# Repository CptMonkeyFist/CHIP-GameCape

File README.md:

# CHIP-GameCape

This is a cape being designed for the CHIP embedded computer. See the LICENSE.txt file for license details.

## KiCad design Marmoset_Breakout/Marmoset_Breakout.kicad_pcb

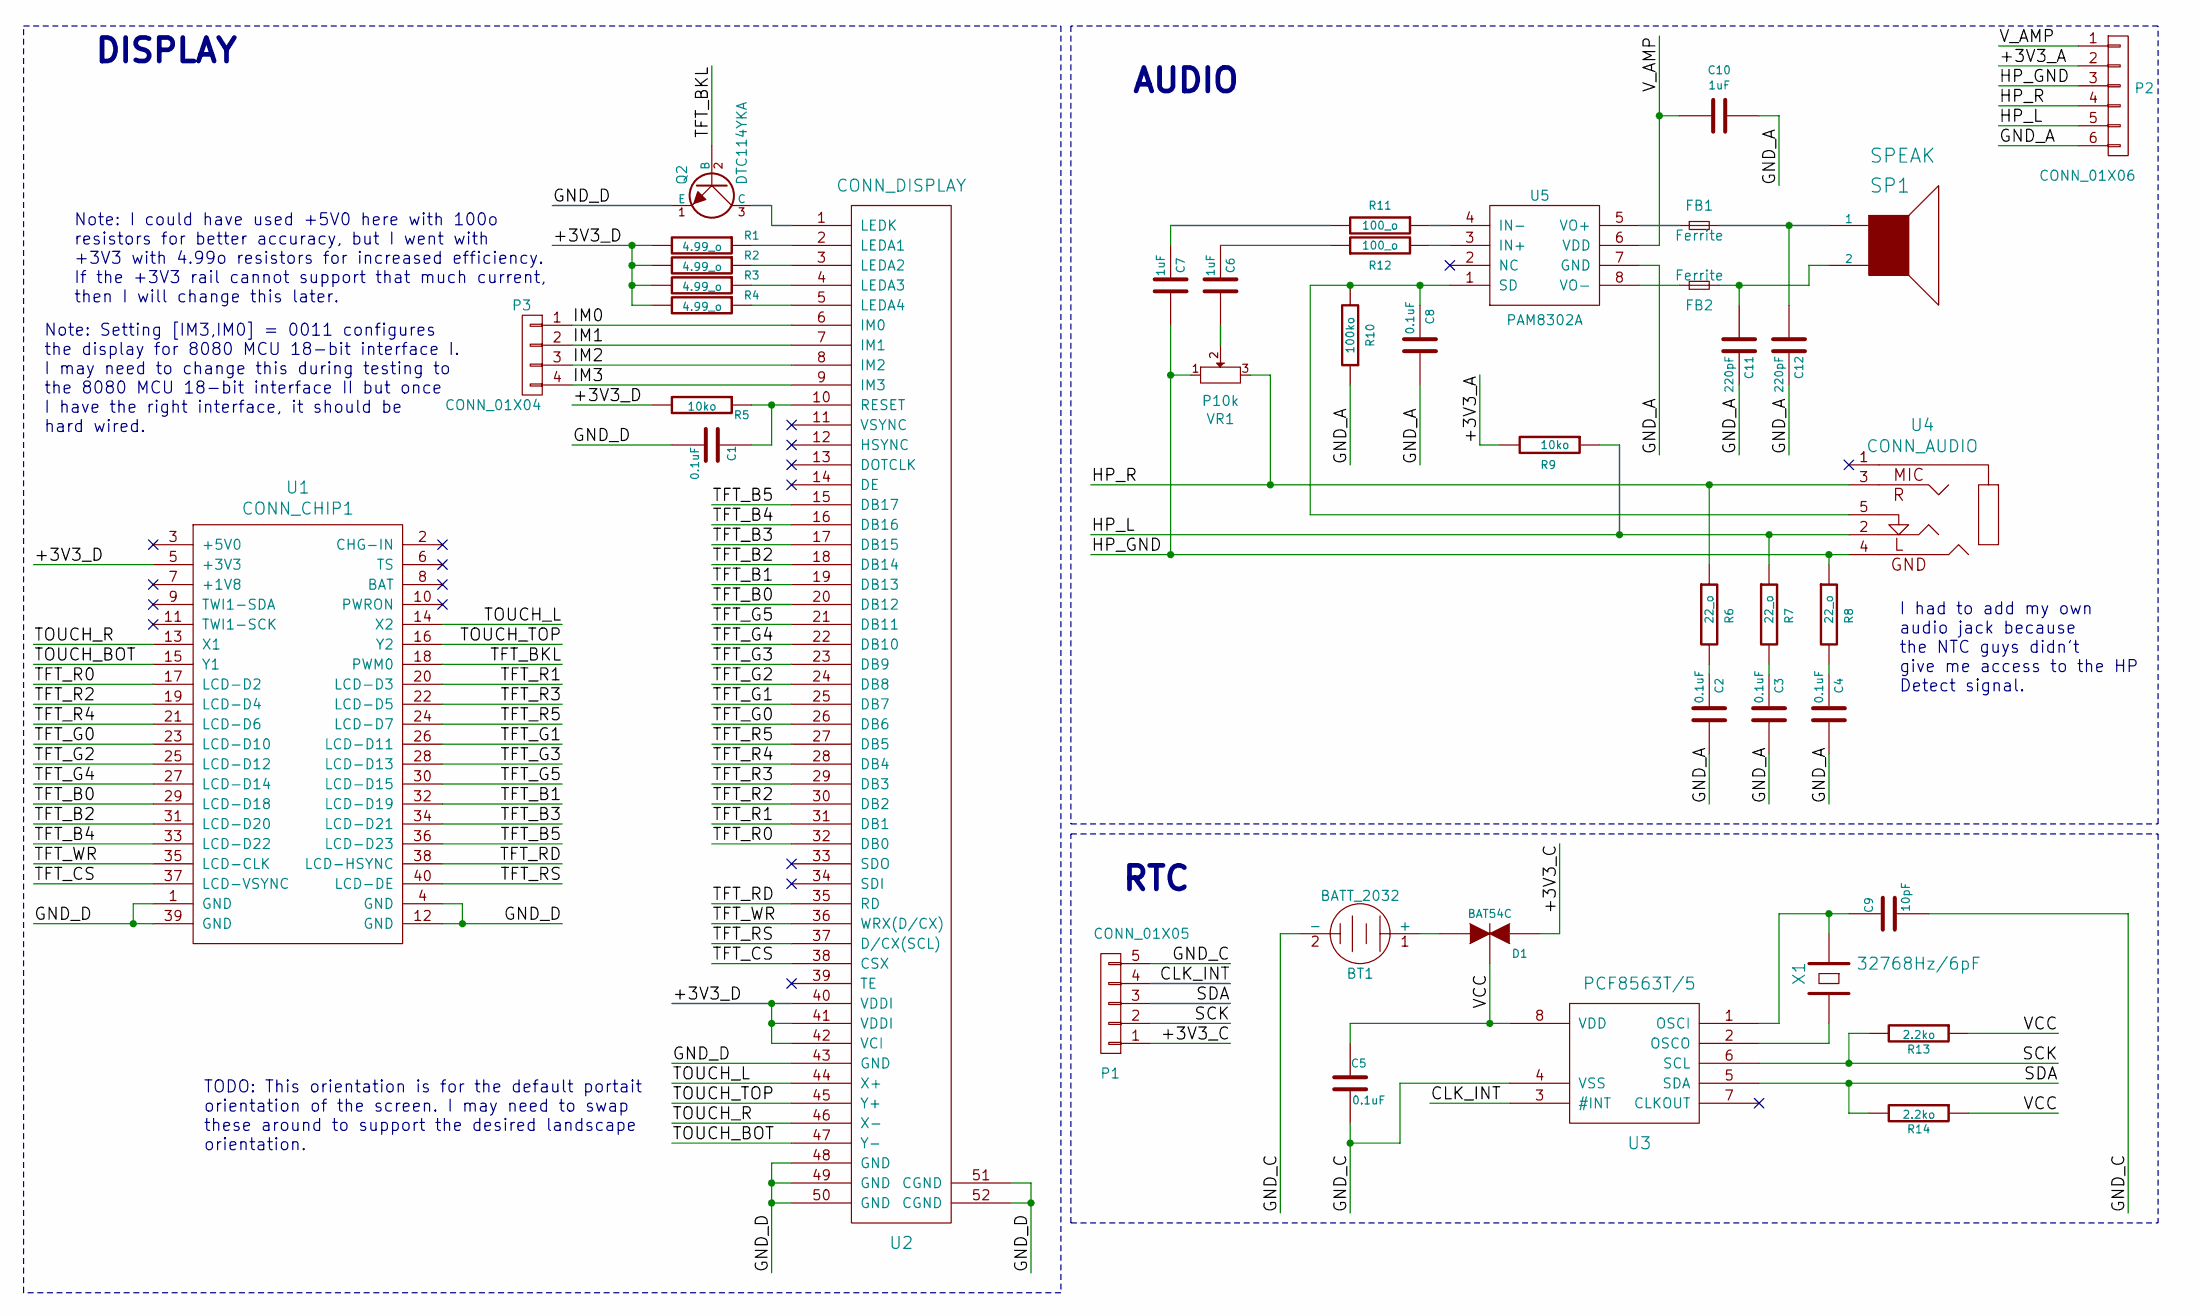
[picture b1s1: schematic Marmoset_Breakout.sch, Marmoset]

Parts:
BT1: BATT_2032; SMTU2032-LF; Manufacturer Part Number BU2032SM-BT-GTR
C1, C2, C3, C4, C5, C8: 0.1uF; C_0805; Manufacturer Part Number CL21B104KBCNNNC
C6, C7, C10: 1uF; C_0805; Manufacturer Part Number CL21B105KPFNNNE
C9: 10pF; C_0805; Manufacturer Part Number CL21C100JBANNNC
C11, C12: 220pF; C_0805; Manufacturer Part Number CL21C221JBANNNC
D1: BAT54C; SOT-23-3; Manufacturer Part Number BAT54C-7-F
FB1, FB2: Ferrite; C_0805; Manufacturer Part Number BLM21PG121SH1D
P1: CONN_01X05; Pin_Header_Straight_1x05
P2: CONN_01X06; Pin_Header_Straight_1x06
P3: CONN_01X04; Pin_Header_Straight_1x04
Q2: DTC114YKA; SOT-23-3; Manufacturer Part Number DTC114YKAT146
R1, R2, R3, R4: 4.99_o; R_0805; Manufacturer Part Number RC2012F4R99CS
R5, R9: 10ko; R_0805; Manufacturer Part Number ERJ-6ENF1002V
R6, R7, R8: 22_o; R_0805; Manufacturer Part Number ERJ-6ENF22R0V
R10: 100ko; R_0805; Manufacturer Part Number ERJ-6ENF1003V
R11, R12: 100_o; R_0805; Manufacturer Part Number ERJ-6ENF1000V
R13, R14: 2.2ko; R_0805; Manufacturer Part Number ERJ-6ENF2201V
SP1: SPEAK; Pin_Header_Straight_1x02; Manufacturer Part Number 2403 260 00001
U1: CONN_CHIP1; Pin_Header_Straight_2x20; Manufacturer Part Number M20-9762042
U2: CONN_DISPLAY; Manufacturer Part Number 62684-502100ALF
U3: PCF8563T/5; SO-8; Manufacturer Part Number PCF8563T/5
U4: CONN_AUDIO; CONN_HP; Manufacturer Part Number SJ-43515TS-SMT-TR
U5: PAM8302A; SO-8; Manufacturer Part Number PAM8302AADCR
VR1: P10k; Thumb_Pot; Manufacturer Part Number 91AR10KLF
X1: 32768Hz/6pF; ABS25; Manufacturer Part Number ABS25-32.768KHZ-6-T

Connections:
/+3V3_A: P2.2, R9.2
/+3V3_C: D1.2 (A), P1.1
/+3V3_D: R1.2, R2.2, R3.2, R4.2, R5.2, U1.5 (+3V3), U2.40 (VDDI), U2.41 (VDDI), U2.42 (VCI)
/CLK_INT: P1.4, U3.3 (#INT)
/GND_A: C2.2, C3.2, C4.2, C8.2, C10.1, C11.1, C12.1, P2.6, R10.1, U5.7 (GND)
/GND_C: BT1.2 (-), C5.2, C9.2, P1.5, U3.4 (VSS)
/GND_D: C1.2, Q2.1 (E), U1.1 (GND), U1.4 (GND), U1.12 (GND), U1.39 (GND), U2.43 (GND), U2.48 (GND), U2.49 (GND), U2.50 (GND), U2.51 (CGND), U2.52 (CGND)
/HP_GND: C7.2, P2.3, R8.1, U4.4, VR1.1
/HP_L: P2.5, R7.1, R9.1, U4.2
/HP_R: P2.4, R6.1, U4.3, VR1.3
/IM0: P3.1, U2.6 (IM0)
/IM1: P3.2, U2.7 (IM1)
/IM2: P3.3, U2.8 (IM2)
/IM3: P3.4, U2.9 (IM3)
/SCK: P1.2, R13.2, U3.6 (SCL)
/SDA: P1.3, R14.2, U3.5 (SDA)
/TFT_B0: U1.29 (LCD-D18), U2.20 (DB12)
/TFT_B1: U1.32 (LCD-D19), U2.19 (DB13)
/TFT_B2: U1.31 (LCD-D20), U2.18 (DB14)
/TFT_B3: U1.34 (LCD-D21), U2.17 (DB15)
/TFT_B4: U1.33 (LCD-D22), U2.16 (DB16)
/TFT_B5: U1.36 (LCD-D23), U2.15 (DB17)
/TFT_BKL: Q2.2 (B), U1.18 (PWM0)
/TFT_CS: U1.37 (LCD-VSYNC), U2.38 (CSX)
/TFT_G0: U1.23 (LCD-D10), U2.26 (DB6)
/TFT_G1: U1.26 (LCD-D11), U2.25 (DB7)
/TFT_G2: U1.25 (LCD-D12), U2.24 (DB8)
/TFT_G3: U1.28 (LCD-D13), U2.23 (DB9)
/TFT_G4: U1.27 (LCD-D14), U2.22 (DB10)
/TFT_G5: U1.30 (LCD-D15), U2.21 (DB11)
/TFT_R0: U1.17 (LCD-D2), U2.32 (DB0)
/TFT_R1: U1.20 (LCD-D3), U2.31 (DB1)
/TFT_R2: U1.19 (LCD-D4), U2.30 (DB2)
/TFT_R3: U1.22 (LCD-D5), U2.29 (DB3)
/TFT_R4: U1.21 (LCD-D6), U2.28 (DB4)
/TFT_R5: U1.24 (LCD-D7), U2.27 (DB5)
/TFT_RD: U1.38 (LCD-HSYNC), U2.35 (RD)
/TFT_RS: U1.40 (LCD-DE), U2.37 (D/CX(SCL))
/TFT_WR: U1.35 (LCD-CLK), U2.36 (WRX(D/CX))
/TOUCH_BOT: U1.15 (Y1), U2.47 (Y-)
/TOUCH_L: U1.14 (X2), U2.44 (X+)
/TOUCH_R: U1.13 (X1), U2.46 (X-)
/TOUCH_TOP: U1.16 (Y2), U2.45 (Y+)
/VCC: C5.1, D1.3 (K), R13.1, R14.1, U3.8 (VDD)
/V_AMP: C10.2, P2.1, U5.6 (VDD)
unnamed: BT1.1 (+), D1.1 (A)
unnamed: C1.1, R5.1, U2.10 (RESET)
unnamed: C2.1, R6.2
unnamed: C3.1, R7.2
unnamed: C4.1, R8.2
unnamed: C6.1, R12.1
unnamed: C6.2, VR1.2
unnamed: C7.1, R11.2
unnamed: C8.1, R10.2, U4.5, U5.1 (SD)
unnamed: C9.1, U3.1 (OSCI), X1.1
unnamed: C11.2, FB2.2, SP1.2
unnamed: C12.2, FB1.2, SP1.1
unnamed: FB1.1, U5.5 (VO+)
unnamed: FB2.1, U5.8 (VO-)
unnamed: Q2.3 (C), U2.1 (LEDK)
unnamed: R1.1, U2.2 (LEDA1)
unnamed: R2.1, U2.3 (LEDA2)
unnamed: R3.1, U2.4 (LEDA3)
unnamed: R4.1, U2.5 (LEDA4)
unnamed: R11.1, U5.4 (IN-)
unnamed: R12.2, U5.3 (IN+)
unnamed: U3.2 (OSCO), X1.2

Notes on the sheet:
Note: Setting [IM3,IM0] = 0011 configures the display for 8080 MCU 18-bit interface I. I may need to change this during testing to the 8080 MCU 18-bit interface II but once I have the right interface, it should be hard wired.
TODO: This orientation is for the default portait orientation of the screen. I may need to swap these around to support the desired landscape orientation.
Note: I could have used +5V0 here with 100o resistors for better accuracy, but I went with +3V3 with 4.99o resistors for increased efficiency. If the +3V3 rail cannot support that much current, then I will change this later.
DISPLAY
AUDIO
I had to add my own audio jack because the NTC guys didn't give me access to the HP Detect signal.
RTC

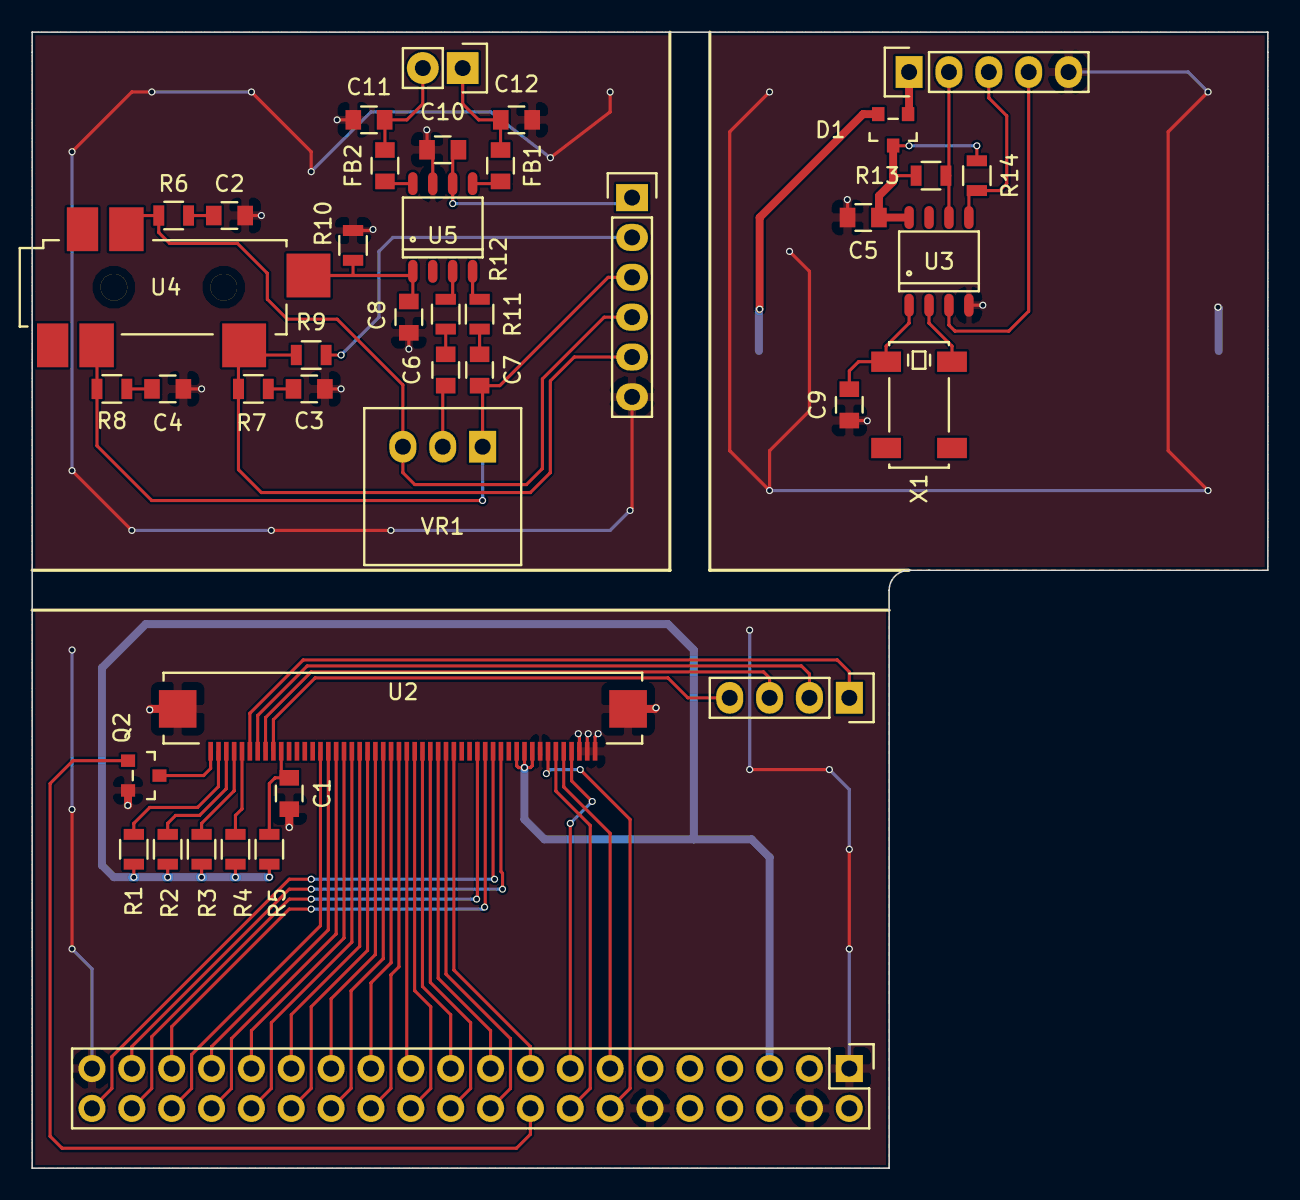
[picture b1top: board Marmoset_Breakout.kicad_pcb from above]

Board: 2 copper layers, 78.7 x 72.4 mm, 42 parts (1 on the bottom side), 67 nets.

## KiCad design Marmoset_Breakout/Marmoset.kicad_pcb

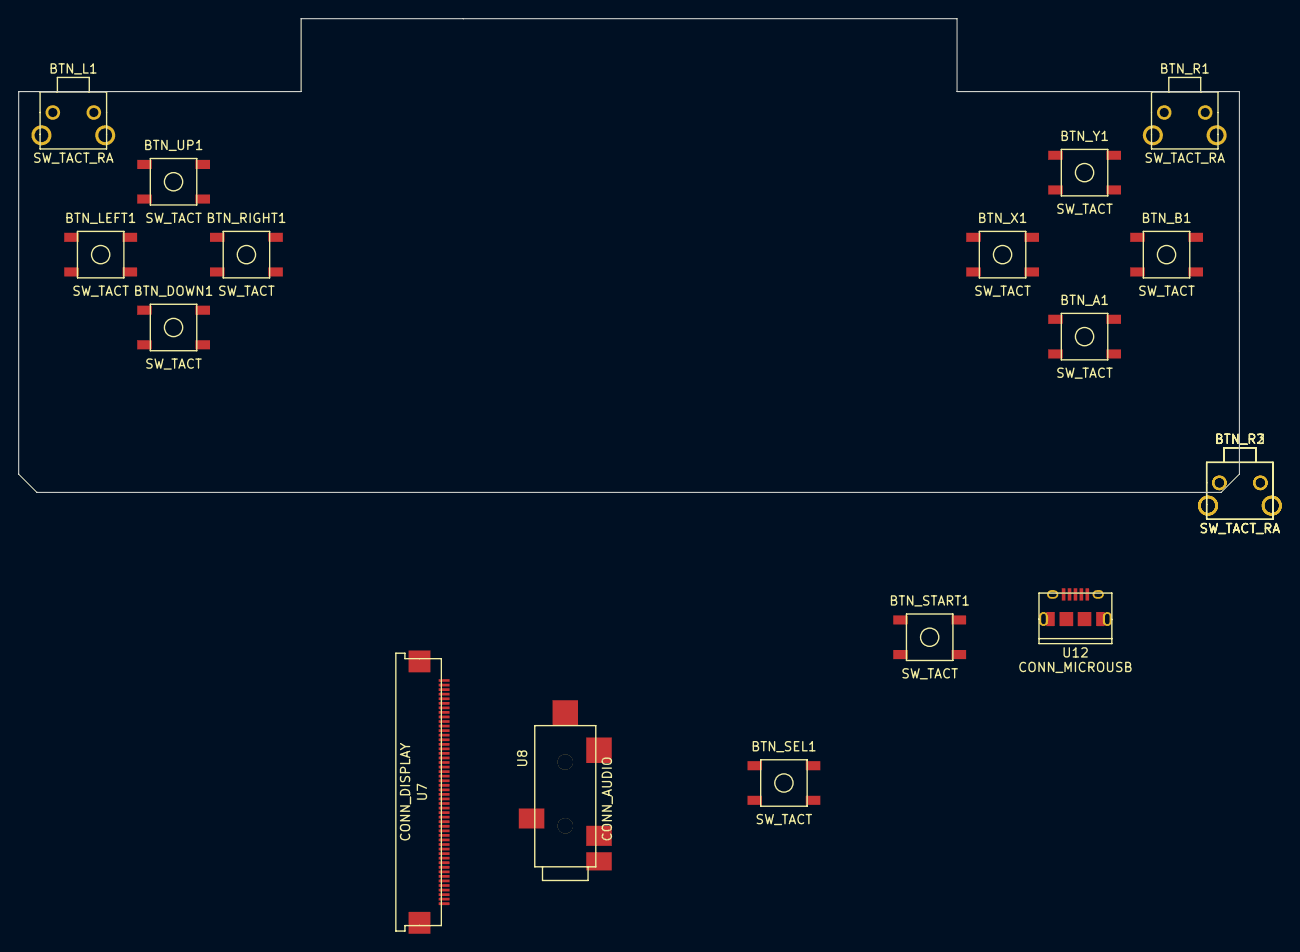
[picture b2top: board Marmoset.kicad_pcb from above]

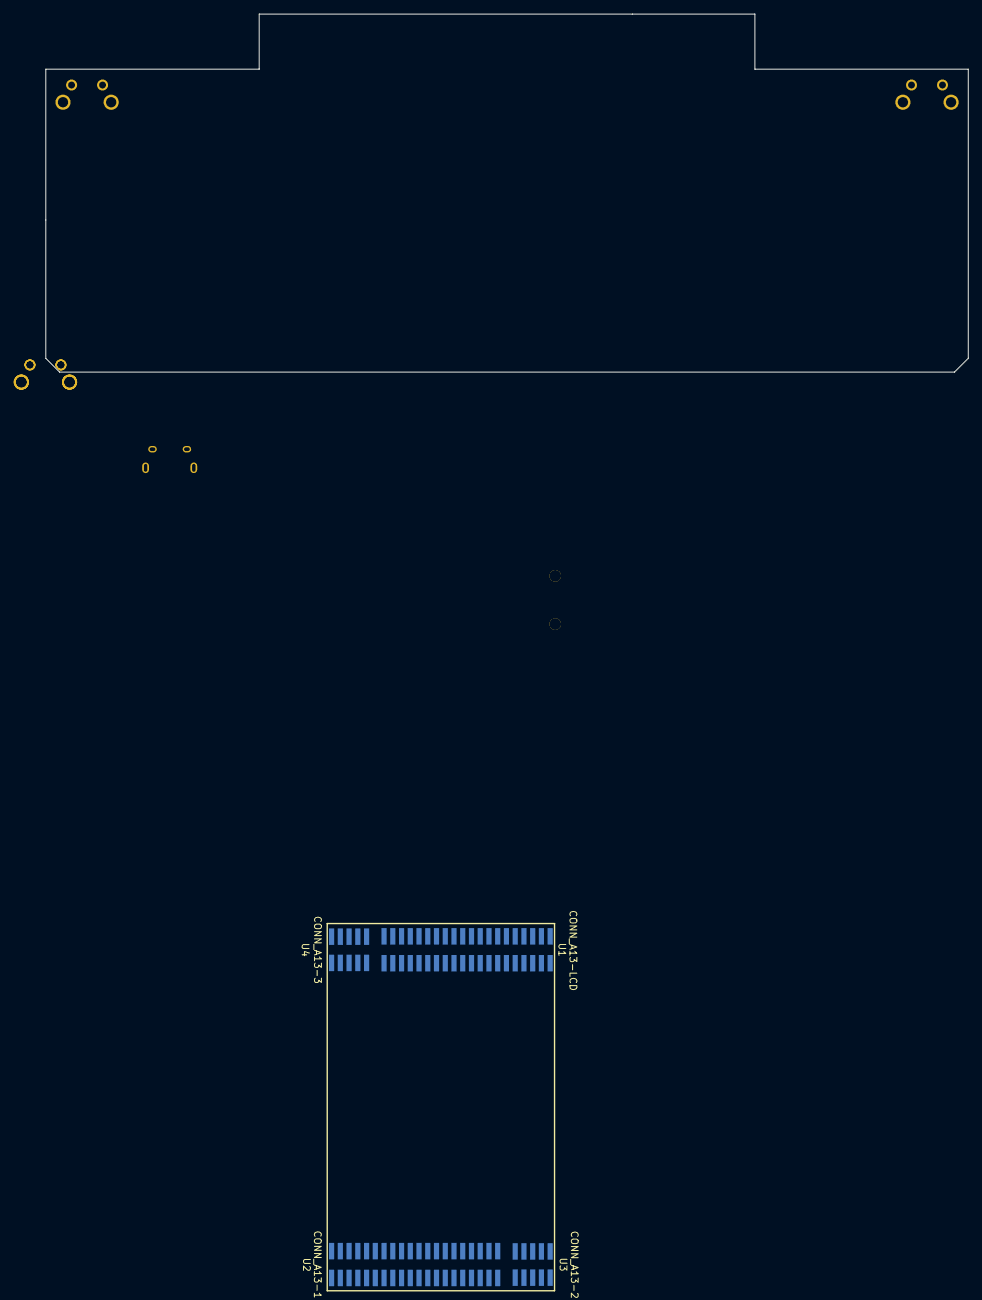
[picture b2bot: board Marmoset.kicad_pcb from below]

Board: 2 copper layers, 134.0 x 52.0 mm, 21 parts (4 on the bottom side), 47 nets, no tracks yet.

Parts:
BTN_A1: SW_TACT
BTN_B1: SW_TACT
BTN_DOWN1: SW_TACT
BTN_L1: SW_TACT_RA
BTN_LEFT1: SW_TACT
BTN_R1, BTN_R2, BTN_R3: SW_TACT_RA
BTN_RIGHT1: SW_TACT
BTN_SEL1: SW_TACT
BTN_START1: SW_TACT
BTN_UP1: SW_TACT
BTN_X1: SW_TACT
BTN_Y1: SW_TACT
U1: CONN_A13-LCD; CONN_A13_2x20
U2: CONN_A13-1; CONN_A13_2x20
U3: CONN_A13-2; CONN_A13_2x5
U4: CONN_A13-3; CONN_A13_2x5
U7: CONN_DISPLAY
U8: CONN_AUDIO
U12: CONN_MICROUSB

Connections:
/Marmoset_Display/+3V3: U1.3, U7.6, U7.7
/Marmoset_Display/CGND: U7.51, U7.52
/Marmoset_Display/TFT_B0: U1.23, U7.20
/Marmoset_Display/TFT_B1: U1.24, U7.19
/Marmoset_Display/TFT_B2: U1.25, U7.18
/Marmoset_Display/TFT_B3: U1.26, U7.17
/Marmoset_Display/TFT_B4: U1.27, U7.16
/Marmoset_Display/TFT_B5: U1.28, U7.15
/Marmoset_Display/TFT_CS: U1.30, U7.38
/Marmoset_Display/TFT_G0: U1.15, U7.26
/Marmoset_Display/TFT_G1: U1.16, U7.25
/Marmoset_Display/TFT_G2: U1.17, U7.24
/Marmoset_Display/TFT_G3: U1.18, U7.23
/Marmoset_Display/TFT_G4: U1.19, U7.22
/Marmoset_Display/TFT_G5: U1.20, U7.21
/Marmoset_Display/TFT_R0: U1.7, U7.32
/Marmoset_Display/TFT_R1: U1.8, U7.31
/Marmoset_Display/TFT_R2: U1.9, U7.30
/Marmoset_Display/TFT_R3: U1.10, U7.29
/Marmoset_Display/TFT_R4: U1.11, U7.28
/Marmoset_Display/TFT_R5: U1.12, U7.27
/Marmoset_Display/TFT_RD: U1.29, U7.35
/Marmoset_Display/TFT_RS: U1.32, U7.37
/Marmoset_Display/TFT_WR: U1.31, U7.36
/Marmoset_Display/TOUCH_BOT: U1.39, U7.47
/Marmoset_Display/TOUCH_L: U1.38, U7.44
/Marmoset_Display/TOUCH_R: U1.37, U7.46
/Marmoset_Display/TOUCH_TOP: U1.40, U7.45
/Marmoset_PWR-USB/UDP0: U3.1, U12.3
/Marmoset_Wifi-Input/+3V3: BTN_A1.2, BTN_B1.2, BTN_DOWN1.2, BTN_L1.2, BTN_LEFT1.2, BTN_R1.2, BTN_R2.2, BTN_R3.2, BTN_RIGHT1.2, BTN_SEL1.2, BTN_START1.2, BTN_UP1.2, BTN_X1.2, BTN_Y1.2
/Marmoset_Wifi-Input/BTN_A: BTN_A1.1, U2.6
/Marmoset_Wifi-Input/BTN_B: BTN_B1.1, U2.8
/Marmoset_Wifi-Input/BTN_DOWN: BTN_DOWN1.1, U2.11
/Marmoset_Wifi-Input/BTN_L: BTN_L1.1, U2.14
/Marmoset_Wifi-Input/BTN_LEFT: BTN_LEFT1.1, U2.13
/Marmoset_Wifi-Input/BTN_R: BTN_R1.1, U2.16
/Marmoset_Wifi-Input/BTN_RIGHT: BTN_RIGHT1.1, U2.15
/Marmoset_Wifi-Input/BTN_SELECT: BTN_SEL1.1, U2.20
/Marmoset_Wifi-Input/BTN_START: BTN_START1.1, U2.18
/Marmoset_Wifi-Input/BTN_UP: BTN_UP1.1, U2.9
/Marmoset_Wifi-Input/BTN_VOL+: BTN_R2.1, U2.22
/Marmoset_Wifi-Input/BTN_VOL-: BTN_R3.1, U2.24
/Marmoset_Wifi-Input/BTN_X: BTN_X1.1, U2.10
/Marmoset_Wifi-Input/BTN_Y: BTN_Y1.1, U2.12
GND: U1.2, U1.4, U2.2, U7.8, U7.9, U7.43, U7.48, U7.49, U7.50
GNDPWR: U12.6, U12.7, U12.8, U12.9
unnamed: U7.40, U7.41, U7.42

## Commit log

2016-06-14 Init
2016-06-20 Added Breakout board KiCad project.
2016-06-20 Added Breakout Schematic
2016-06-30 Added LCD interface document.
2016-07-08 Fixed unconnected LCD Power Enable signal. Fixed audio schematic and redid layout accordingly.
2016-07-08 Fixed Shutdown circuit for audio amp to use negative logic (as specified in datasheet) Fixed debouncing circuit for headphone ground pin. Added another pin to audio board to allow me to choose voltag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
2016-07-28 Changed Speaker used and updated BOM/Schematic.
